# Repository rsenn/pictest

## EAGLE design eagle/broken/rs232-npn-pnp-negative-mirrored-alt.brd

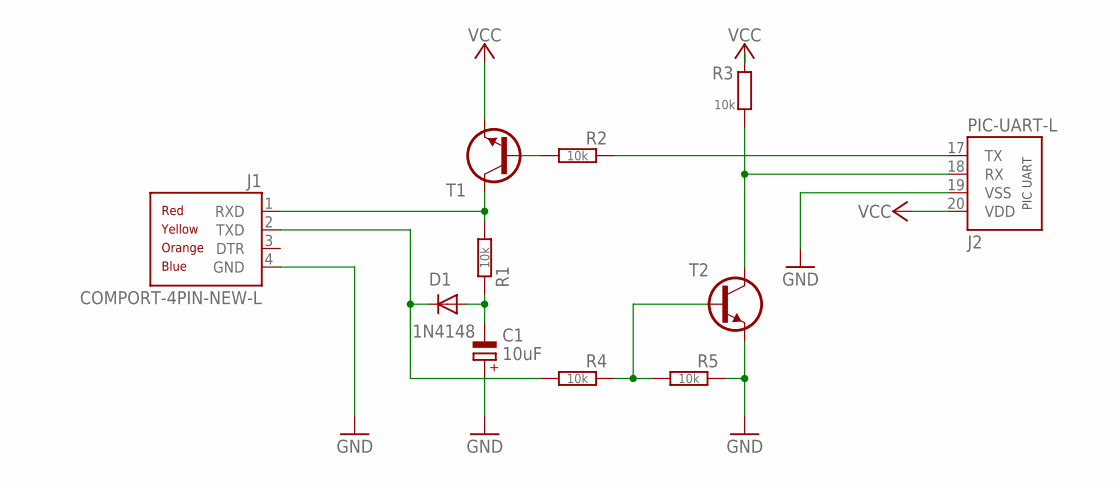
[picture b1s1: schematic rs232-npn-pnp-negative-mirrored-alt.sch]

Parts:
C1: 10uF; E2,5-5
D1: 1N4148; DO34-5V
J1: COMPORT-4PIN-NEW-L; RS232-4PIN-NEW-L
J2: PIC-UART-L
R1, R2, R4: 10k; 0202/7
R3, R5: 10k; 0202/7-V
T1, T2: BC547; TO92-CBE

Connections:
-12V: C1.-, D1.A, R1.1
GND: C1.+, J1.4 (GND), J2.19 (VSS), R5.1, T2.E
unnamed: R2.2, T1.B
unnamed: R4.1, R5.2, T2.B
RX: J2.18 (RX), R3.1, T2.C
RXD: J1.1 (RXD), R1.2, T1.C
TX: J2.17 (TX), R2.1
TXD: D1.C, J1.2 (TXD), R4.2
VCC: J2.20 (VDD), R3.2, T1.E

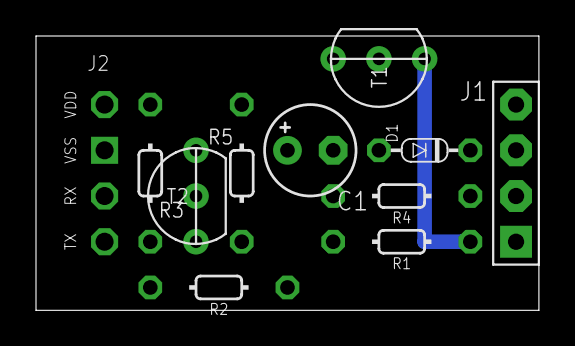
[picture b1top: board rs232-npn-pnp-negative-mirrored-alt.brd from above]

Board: 2 copper layers, 27.9 x 15.2 mm, 11 parts (0 on the bottom side), 9 nets.

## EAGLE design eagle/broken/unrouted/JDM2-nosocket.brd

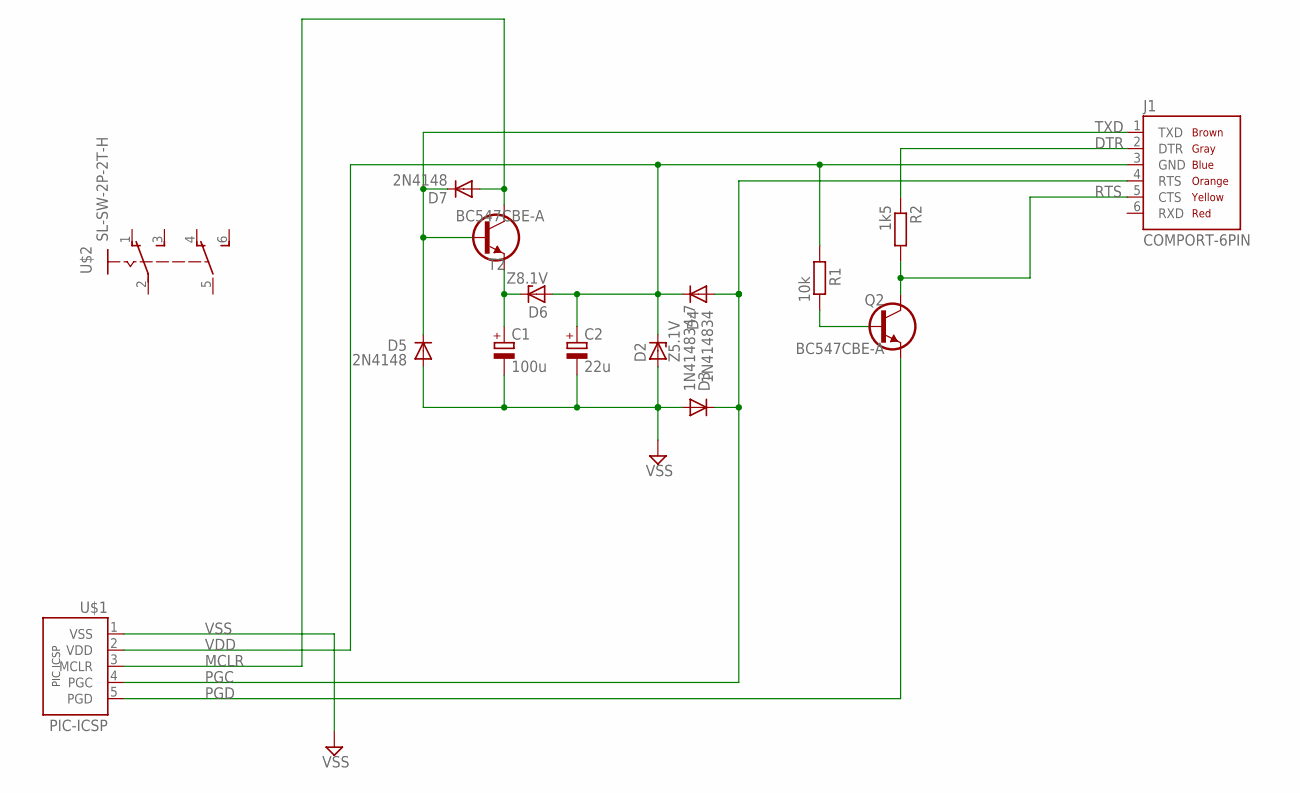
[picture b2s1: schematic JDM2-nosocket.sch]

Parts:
C1: 100u; E2,5-5
C2: 22u; E2,5-4
D2: Z5.1V; DO35Z2_54
D3: 1N414834-7; DO34-7
D4: 1N414834; DO34-7
D5: 2N4148; DO34-7
D6: Z8.1V; DO35Z2_54
D7: 2N4148; DO35-2_54
J1: COMPORT-6PIN; RS232-6PIN
Q2: BC547CBE-A; TO92-CBE-A
R1: 10k; 0204/7
R2: 1k5; 0207/7
T2: BC547CBE-A; TO92-CBE-A
U$1: PIC-ICSP; CONN-5P
U$2: SL-SW-2P-2T-H; SLSW-2P2T-H

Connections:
DTR: J1.2 (DTR), R2.1
MCLR: D7.A, T2.C, U$1.3 (MCLR)
unnamed: Q2.B, R1.1
unnamed: C1.+, D6.C, T2.E
PGC: D3.C, D4.A, J1.4 (RTS), U$1.4 (PGC)
PGD: Q2.E, U$1.5 (PGD)
RTS: J1.5 (CTS), Q2.C, R2.2
TXD: D5.C, D7.C, J1.1 (TXD), T2.B
VDD: C2.+, D2.C, D4.C, D6.A, R1.2, U$1.2 (VDD)
VSS: C1.-, C2.-, D2.A, D3.A, D5.A, U$1.1 (VSS)

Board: 2 copper layers, 15 parts (0 on the bottom side), 10 nets, no tracks yet.

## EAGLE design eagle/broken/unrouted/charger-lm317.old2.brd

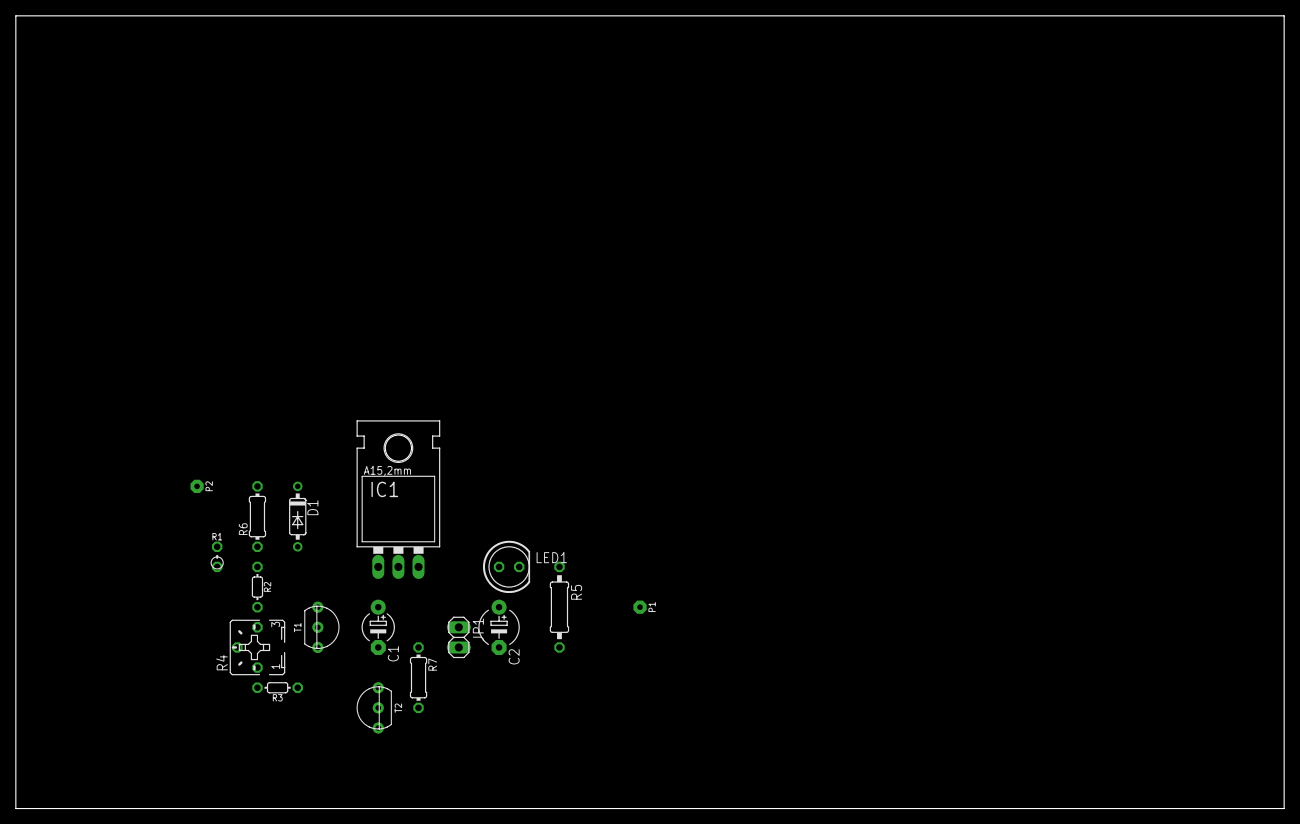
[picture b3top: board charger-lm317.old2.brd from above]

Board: 2 copper layers, 160.0 x 100.0 mm, 17 parts (0 on the bottom side), 11 nets, no tracks yet.

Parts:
C1: E5-4
C2: E5-5
D1: 1N4148-7; DO35-7
IC1: 317TL
JP1: 1X02
LED1: LED5MM
P1, P2: SPAD
R1: 0202/2V
R2, R3: 2.2k; 0202/5
R4: B25P
R5: 0207/10
R6, R7: 0204/7
T1, T2: BC547CBE; TO92-CBE

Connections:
unnamed: C1.+, IC1.1, R4.S, T1.C
unnamed: IC1.2, JP1.1, R3.1
unnamed: C1.-, C2.-, D1.A, R1.2, R6.1, T1.E
unnamed: R2.2, R4.E
unnamed: JP1.2, R1.1, R2.1, R7.1, T1.B
unnamed: D1.C, P2.1, R6.2, T2.E
unnamed: R5.2, T2.C
unnamed: LED1.K, R5.1
unnamed: C2.+, IC1.3, LED1.A, P1.1
unnamed: R3.2, R4.A
unnamed: R7.2, T2.B

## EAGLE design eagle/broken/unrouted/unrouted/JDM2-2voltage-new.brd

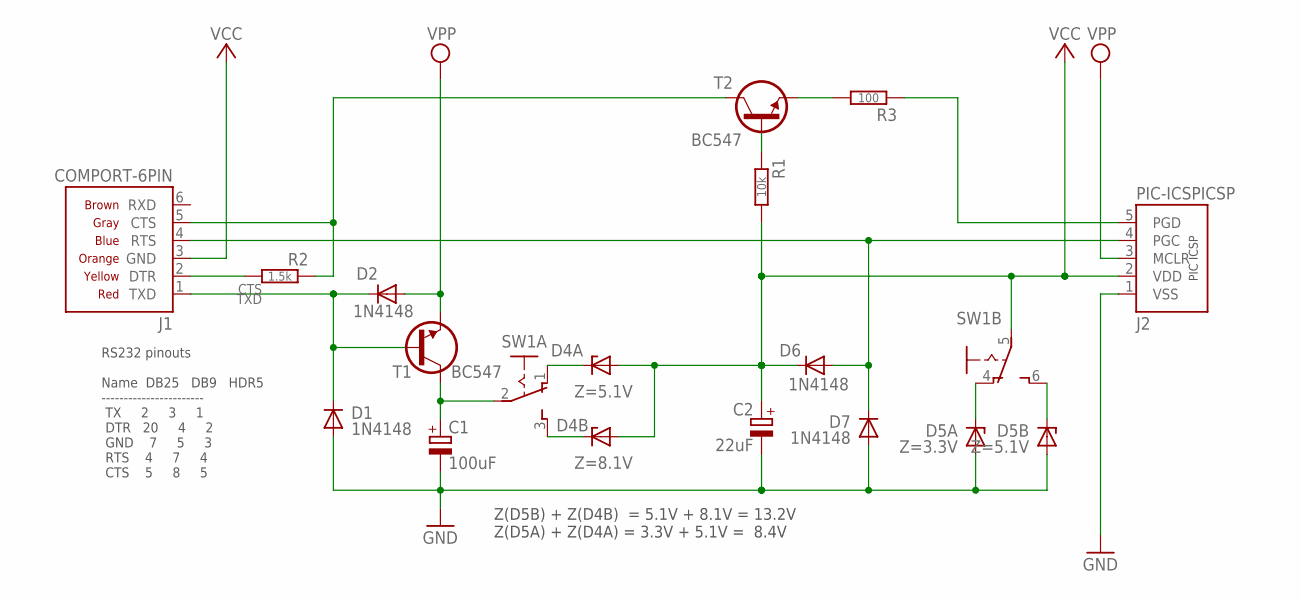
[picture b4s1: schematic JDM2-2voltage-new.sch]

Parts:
C1: 100uF; E2,5-5
C2: 22uF; E2,5-4
D1, D7: 1N4148; DO34-5V
D2, D6: 1N4148; DO34-7V
D4A: Z=5.1V; DO34Z5
D4B: Z=8.1V; DO34Z5
D5A: Z=3.3V; DO34Z7V
D5B: Z=5.1V; DO34Z7V
J1: COMPORT-6PIN; RS232-6PIN
J2: PIC-ICSPICSP; PIC-ICSP
R1: 10k; 0202/7-V
R2: 1.5k; 0202/7-V
R3: 100; 0202/7
SW1: SL-SW-2P-2T-S; SLSW-2P2T-H
T1, T2: BC547; TO92-CBE

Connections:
/MCLR: D2.A, J2.3 (MCLR), T1.E
CLK: D6.A, D7.C, J1.4 (RTS), J2.4 (PGC)
CTS: J1.5 (CTS), R2.1, T2.C
DATA: R3.2, T2.E
GND: C1.-, C2.-, D1.A, D5A.A, D5B.A, D7.A, J2.1 (VSS)
unnamed: R1.1, T2.B
unnamed: D5A.C, SW1.4 (O)
unnamed: D4B.C, SW1.3 (S)
unnamed: C1.+, SW1.2, T1.C
unnamed: D5B.C, SW1.6 (S)
unnamed: J1.2 (DTR), R2.2
PGD: J2.5 (PGD), R3.1
TXD: D1.C, D2.C, J1.1 (TXD), T1.B
VCC: C2.+, D4A.A, D4B.A, D6.C, J1.3 (GND), J2.2 (VDD), R1.2, SW1.5
VPP: D4A.C, SW1.1 (O)

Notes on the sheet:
RS232 pinouts Name DB25 DB9 HDR5 ----------------------- TX 2 3 1 DTR 20 4 2 GND 7 5 3 RTS 4 7 4 CTS 5 8 5
Z(D5B) + Z(D4B) = 5.1V + 8.1V = 13.2V Z(D5A) + Z(D4A) = 3.3V + 5.1V = 8.4V

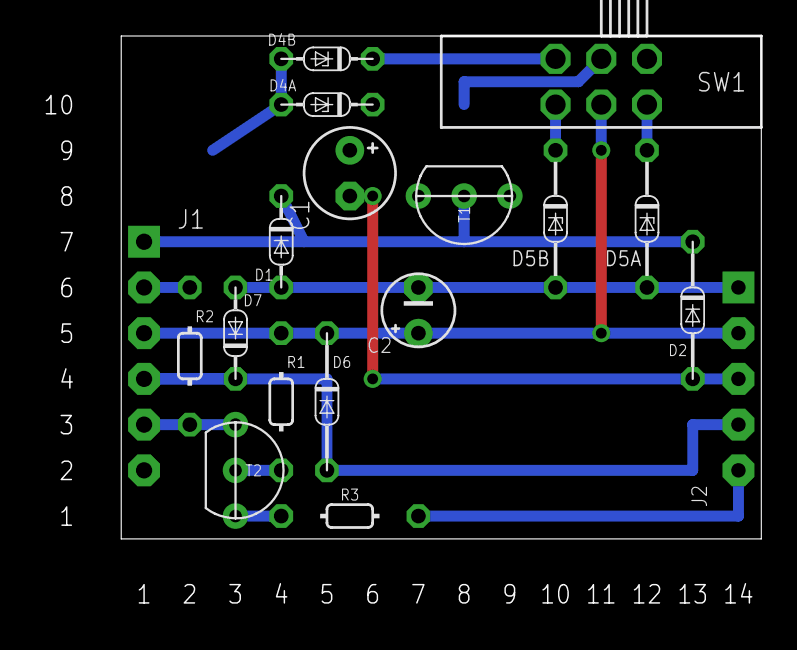
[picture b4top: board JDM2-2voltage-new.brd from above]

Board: 2 copper layers, 35.6 x 27.9 mm, 18 parts (0 on the bottom side), 15 nets.

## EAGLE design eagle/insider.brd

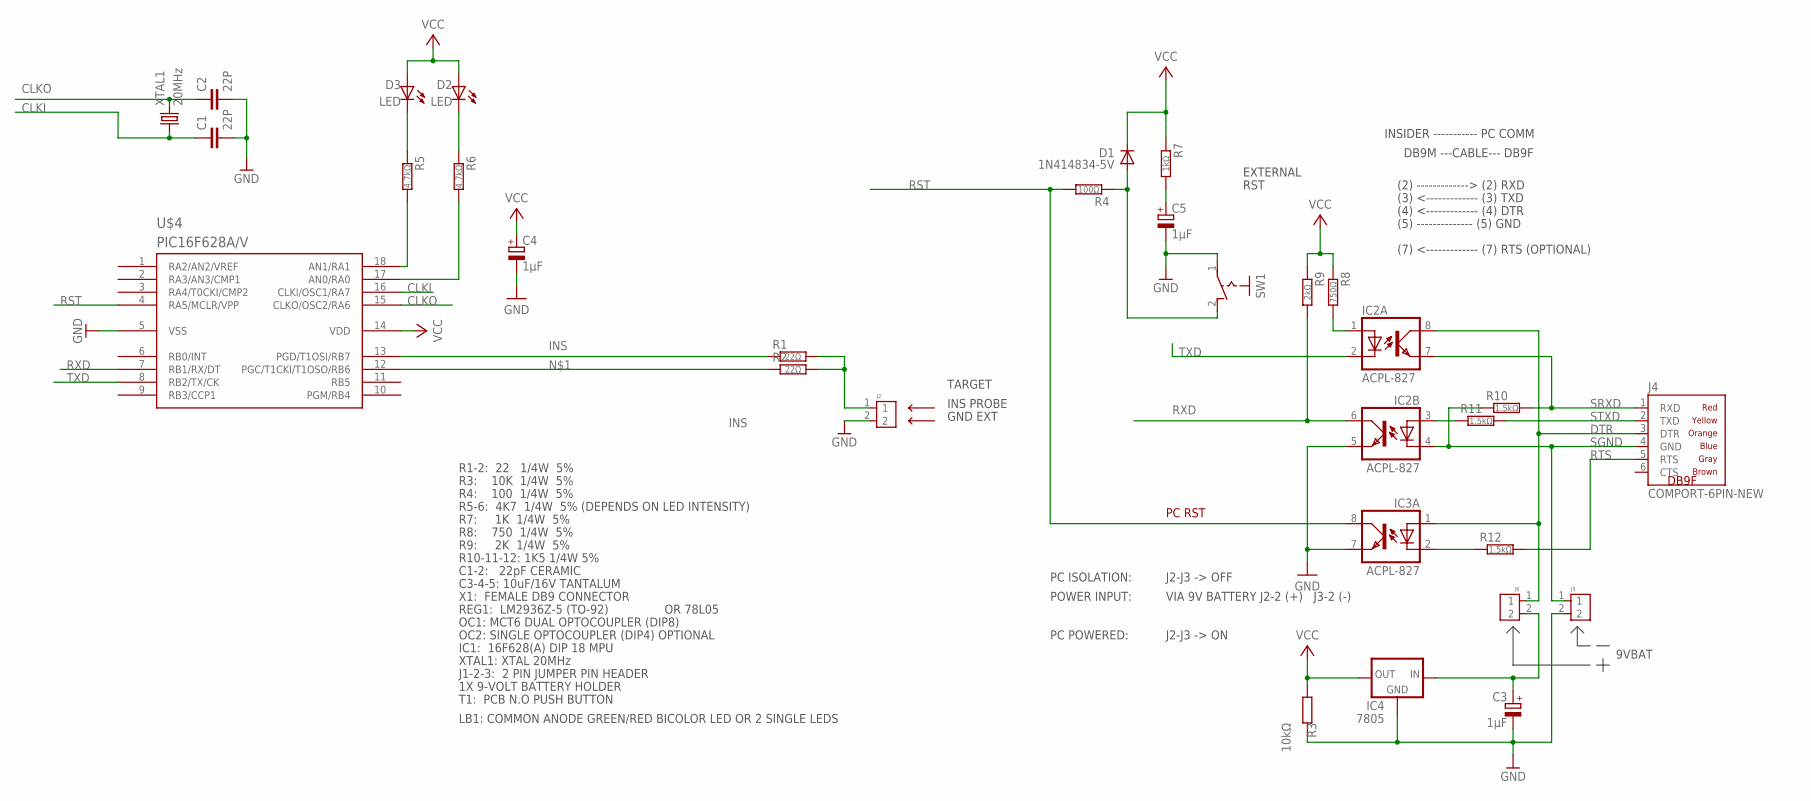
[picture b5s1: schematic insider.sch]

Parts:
C1, C2: 22P; C025-020X036
C3, C4, C5: 1μF; E2.5-4/V
D1: 1N414834-5V; DO34-5V
D2, D3: LED; LED3MM
IC2, IC3: ACPL-827; DIL08
IC4: 7805; TO220
J2, J5, J6: CONN-2P2P/V; CONN-2P-V
J4: COMPORT-6PIN-NEW; RS232-6PIN-NEW
R1, R2: 22Ω; 0204/10
R3: 10kΩ; 0204/10
R4: 100Ω; 0204/15
R5, R6: 4.7kΩ; 0204/10
R7: 1kΩ; 0204/10
R8: 750Ω; 0204/12
R9: 2kΩ; 0204/12
R10, R11, R12: 1.5kΩ; 0204/10
SW1: PB-1P-1T; PB-1P1T
U$4: PIC16F628A/V; DIL18-3/V
XTAL1: 20MHz; HC49

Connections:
CLKI: C1.1, U$4.16 (CLKI/OSC1/RA7), XTAL1.1
CLKO: C2.1, U$4.15 (CLKO/OSC2/RA6), XTAL1.2
DTR: IC2.8 (COL), IC3.1 (A), J4.3 (DTR), J6.1
GND: C1.2, C2.2, C3.-, C4.-, C5.-, IC2.5 (EMIT), IC3.7 (EMIT), IC4.2 (GND), J2.2, J5.2, R3.2, SW1.1, U$4.5 (VSS)
INS: R1.1, U$4.13 (PGD/T1OSI/RB7)
unnamed: R2.1, U$4.12 (PGC/T1CKI/T1OSO/RB6)
unnamed: R5.2, U$4.18 (AN1/RA1)
unnamed: IC2.3 (A), R11.1
unnamed: IC2.1 (A), R8.2
unnamed: IC3.2 (C), R12.1
unnamed: J2.1, R1.2, R2.2
unnamed: R6.2, U$4.17 (AN0/RA0)
unnamed: C5.+, R7.2
unnamed: D2.K (C), R6.1
unnamed: D3.K (C), R5.1
unnamed: D1.A, R4.1, SW1.2 (S)
unnamed: C3.+, IC4.1 (IN), J6.2
RST: IC3.8 (COL), R4.2, U$4.4 (RA5/MCLR/VPP)
RTS: J4.5 (RTS), R12.2
RXD: IC2.6 (COL), R9.2, U$4.7 (RB1/RX/DT)
SGND: IC2.4 (C), J4.4 (GND), J5.1, R10.1
SRXD: IC2.7 (EMIT), J4.1 (RXD), R10.2
STXD: J4.2 (TXD), R11.2
TXD: IC2.2 (C), U$4.8 (RB2/TX/CK)
VCC: C4.+, D1.C, D2.A, D3.A, IC4.3 (OUT), R3.1, R7.1, R8.1, R9.1, U$4.14 (VDD)

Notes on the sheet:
EXTERNAL
RST
9VBAT
GND EXT
INS PROBE
PC ISOLATION:
J2-J3 -> OFF
POWER INPUT:
VIA 9V BATTERY J2-2 (+) J3-2 (-)
PC POWERED:
J2-J3 -> ON
TARGET
PC RST
R1-2: 22 1/4W 5%
R3: 10K 1/4W 5%
R4: 100 1/4W 5%
R5-6: 4K7 1/4W 5% (DEPENDS ON LED INTENSITY)
R7: 1K 1/4W 5%
R8: 750 1/4W 5%
R10-11-12: 1K5 1/4W 5%
R9: 2K 1/4W 5%
C1-2: 22pF CERAMIC
C3-4-5: 10uF/16V TANTALUM
REG1: LM2936Z-5 (TO-92)
OR 78L05
OC1: MCT6 DUAL OPTOCOUPLER (DIP8)
OC2: SINGLE OPTOCOUPLER (DIP4) OPTIONAL
IC1: 16F628(A) DIP 18 MPU
XTAL1: XTAL 20MHz
J1-2-3: 2 PIN JUMPER PIN HEADER
1X 9-VOLT BATTERY HOLDER
LB1: COMMON ANODE GREEN/RED BICOLOR LED OR 2 SINGLE LEDS
X1: FEMALE DB9 CONNECTOR
(2) -------------> (2) RXD
(3) <------------- (3) TXD
(4) <------------- (4) DTR
(5) -------------- (5) GND
INSIDER ----------- PC COMM
DB9M ---CABLE--- DB9F
DB9F

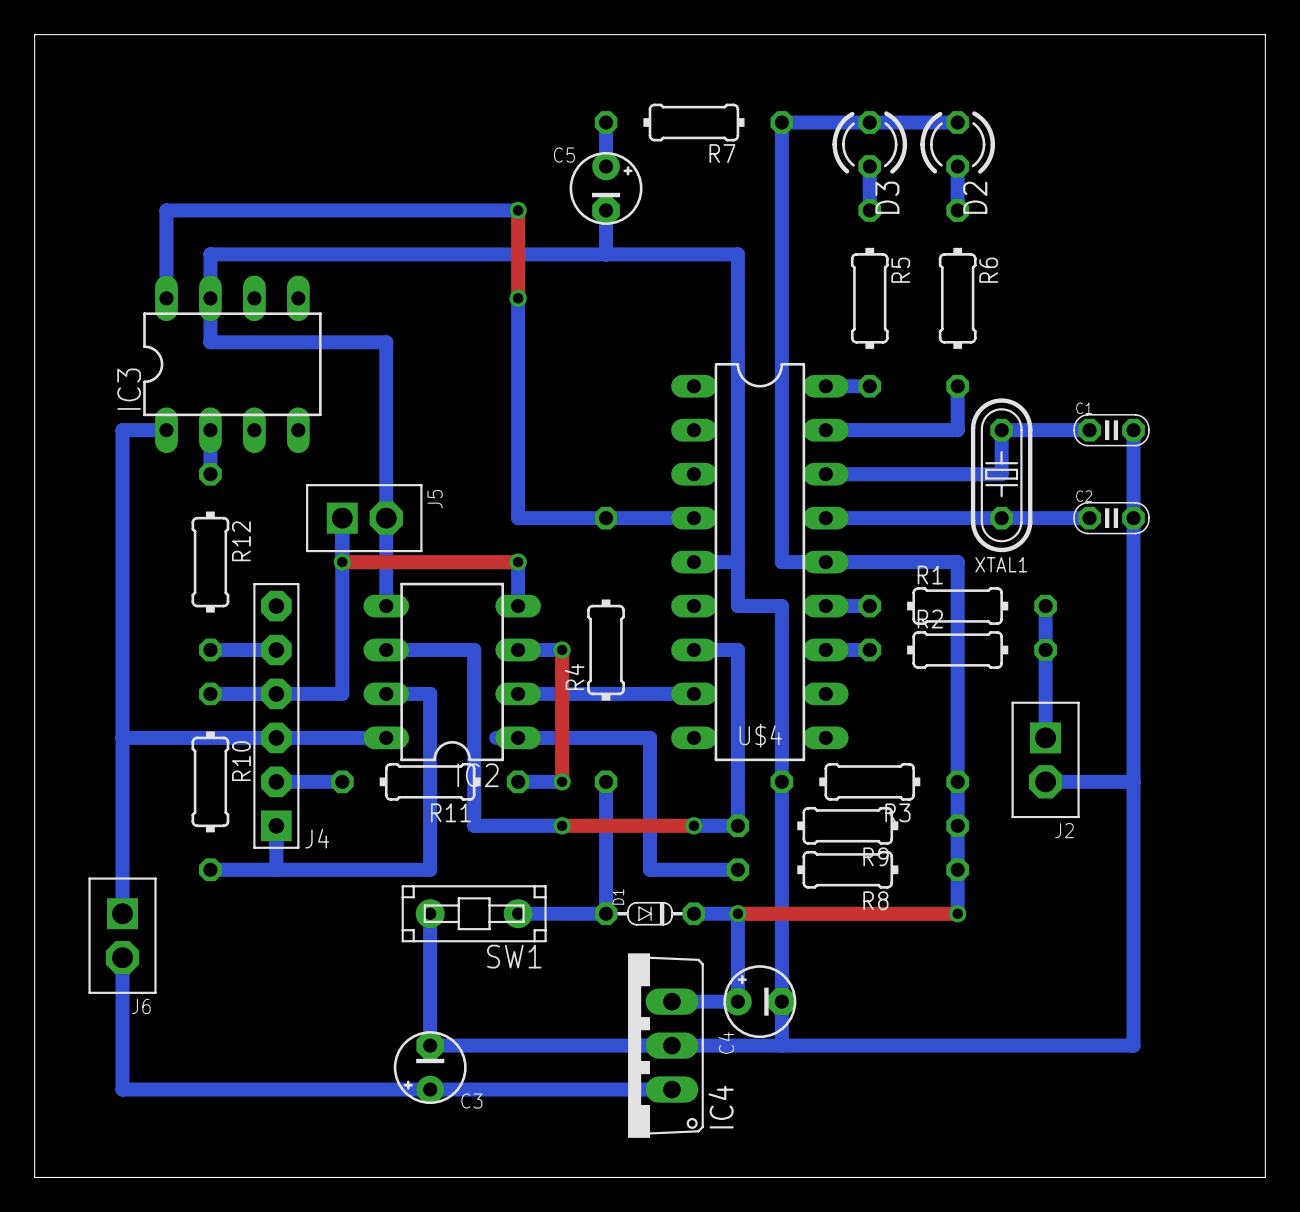
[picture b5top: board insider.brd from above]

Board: 2 copper layers, 71.1 x 66.0 mm, 30 parts (0 on the bottom side), 25 nets.

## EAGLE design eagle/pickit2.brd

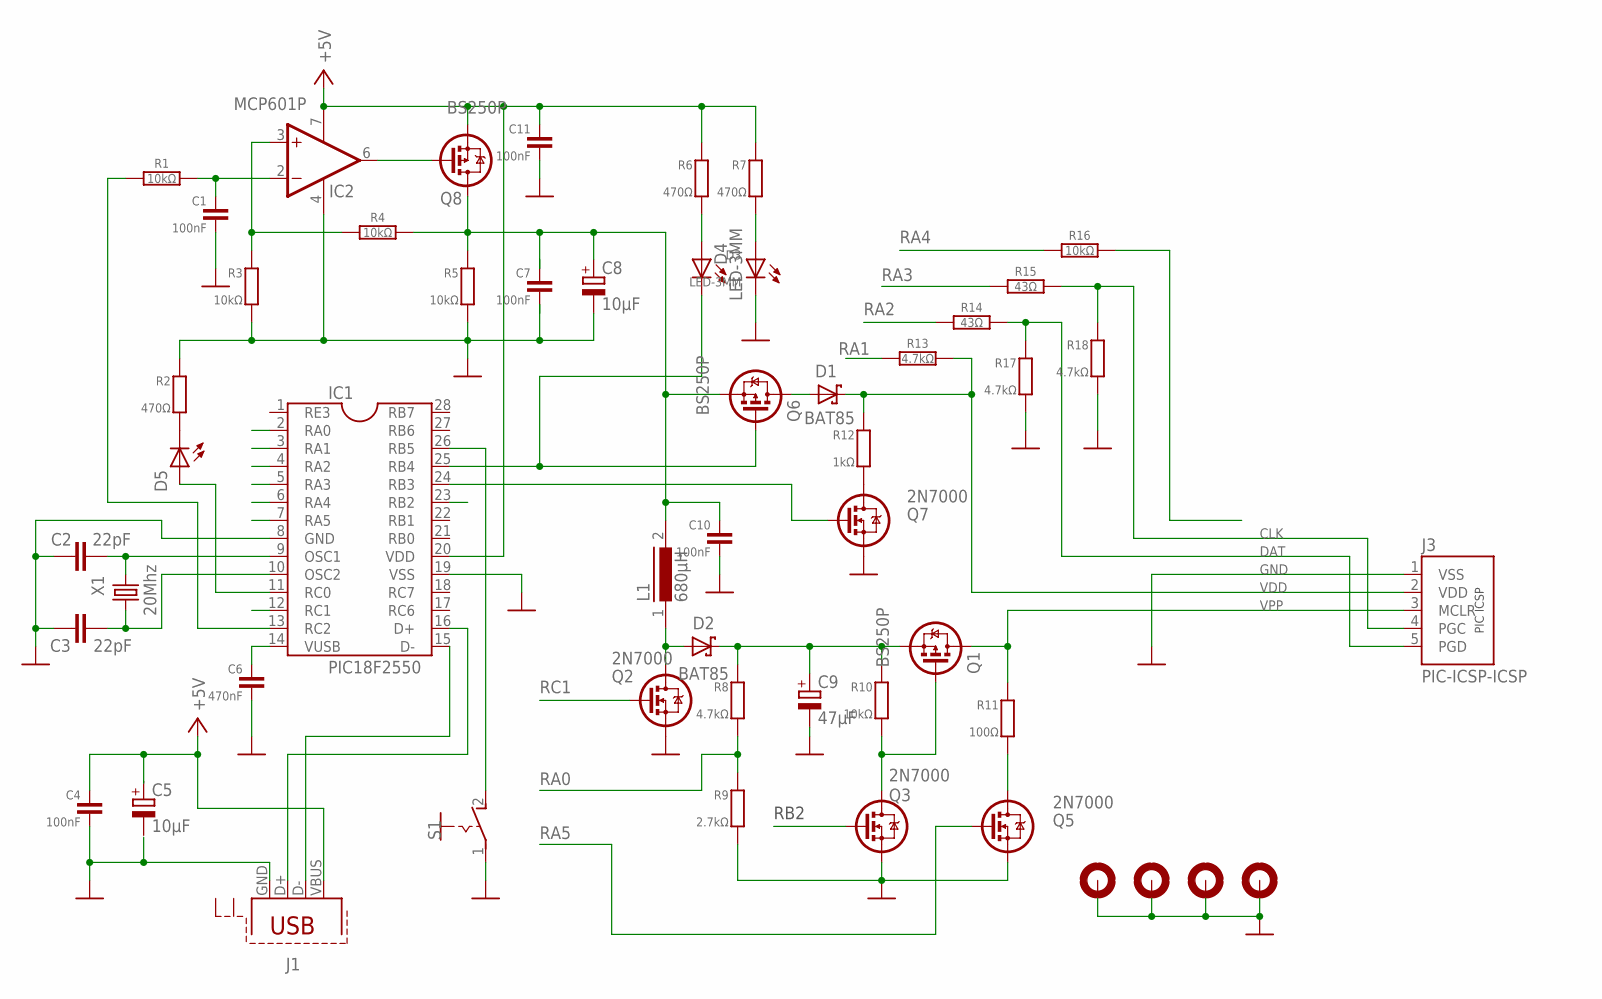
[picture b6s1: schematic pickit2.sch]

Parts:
C1, C4, C7, C10, C11: 100nF; C050-025X075/V
C2, C3: 22pF; C2.5-2
C5, C8: 10μF; E2,5-5
C6: 470nF; C050-025X075/V
C9: 47μF; E2,5-5
D1, D2: BAT85; DO35-10M
D3, D4: LED-3MM; LED_3MM
D5: LED5MM
H1, H2, H3, H4: MOUNT-PAD-ROUND2.8; 2,8-PAD
IC1: PIC18F2550; DIL28
IC2: MCP601P; DIL08M
J1: PN61729-S
J3: PIC-ICSP-ICSP; PIC-ICSP
L1: 680μH; R0608
Q1, Q6, Q8: BS250P; TO92
Q2, Q3, Q5, Q7: 2N7000; TO92
R1, R3, R4, R5, R10, R16: 10kΩ; 0204/10
R2, R6, R7: 470Ω; 0204/10
R8, R13, R17, R18: 4.7kΩ; 0204/10
R9: 2.7kΩ; 0204/10
R11: 100Ω; 0204/10
R12: 1kΩ; 0204/10
R14, R15: 43Ω; 0204/10
S1: PB-1P-1T; PB-1P1T
X1: 20Mhz; HC49

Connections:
+5V: C4.1, C5.+, C11.1, IC1.20 (VDD), IC2.7 (V+), J1.VBUS (1), Q8.3 (S), R6.1, R7.1
GND: C1.2, C2.1, C3.2, C4.2, C6.2, C7.2, C8.-, C9.-, C10.2, C11.2, D3.K (C), H1.B2,8, H2.B2,8, H3.B2,8, H4.B2,8, IC1.8 (GND), IC1.19 (VSS), IC2.4 (V-), J1.GND (4), J3.1 (VSS), Q2.1 (S), Q3.1 (S), Q5.1 (S), Q7.1 (S), R2.1, R3.2, R5.2, R9.2, R17.2, R18.2, S1.1
unnamed: D4.A, R6.2
unnamed: D2.A, L1.1, Q2.3 (D)
unnamed: IC2.6 (OUT), Q8.2 (G)
unnamed: C9.+, D2.C, Q1.3 (S), R8.1, R10.1
unnamed: D3.A, R7.2
unnamed: D5.K (C), R2.2
unnamed: Q5.3 (D), R11.2
unnamed: IC1.15 (D-), J1.D- (2)
unnamed: IC1.16 (D+), J1.D+ (3)
unnamed: Q1.2 (G), Q3.3 (D), R10.2
unnamed: J3.3 (MCLR), Q1.1 (D), R11.1
unnamed: D1.A, Q6.1 (D)
unnamed: D1.C, J3.2 (VDD), R12.1, R13.2
unnamed: Q7.3 (D), R12.2
unnamed: D4.K (C), IC1.25 (RB4), Q6.2 (G)
unnamed: C2.2, IC1.9 (OSC1), X1.2
unnamed: C6.1, IC1.14 (VUSB)
unnamed: IC1.24 (RB3), Q7.2 (G)
unnamed: J3.5 (PGD), R14.2, R17.1
unnamed: J3.4 (PGC), R15.2, R18.1
unnamed: IC2.3 (+IN), R3.1, R4.1
unnamed: C7.1, C8.+, C10.1, L1.2, Q6.3 (S), Q8.1 (D), R4.2, R5.1
unnamed: C3.1, IC1.10 (OSC2), X1.1
unnamed: C1.1, IC2.2 (-IN), R1.2
RA0: IC1.2 (RA0), R8.2, R9.1
RA1: IC1.3 (RA1), R13.1
RA2: IC1.4 (RA2), R14.1
RA3: IC1.5 (RA3), R15.1
RA4: IC1.6 (RA4), R16.1
RA5: IC1.7 (RA5), Q5.2 (G)
RB2: IC1.23 (RB2), Q3.2 (G)
RB5: IC1.26 (RB5), S1.2 (S)
RC0: D5.A, IC1.11 (RC0)
RC1: IC1.12 (RC1), Q2.2 (G)
RC2: IC1.13 (RC2), R1.1

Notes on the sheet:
RB2
VPP
VDD
GND
DAT
CLK

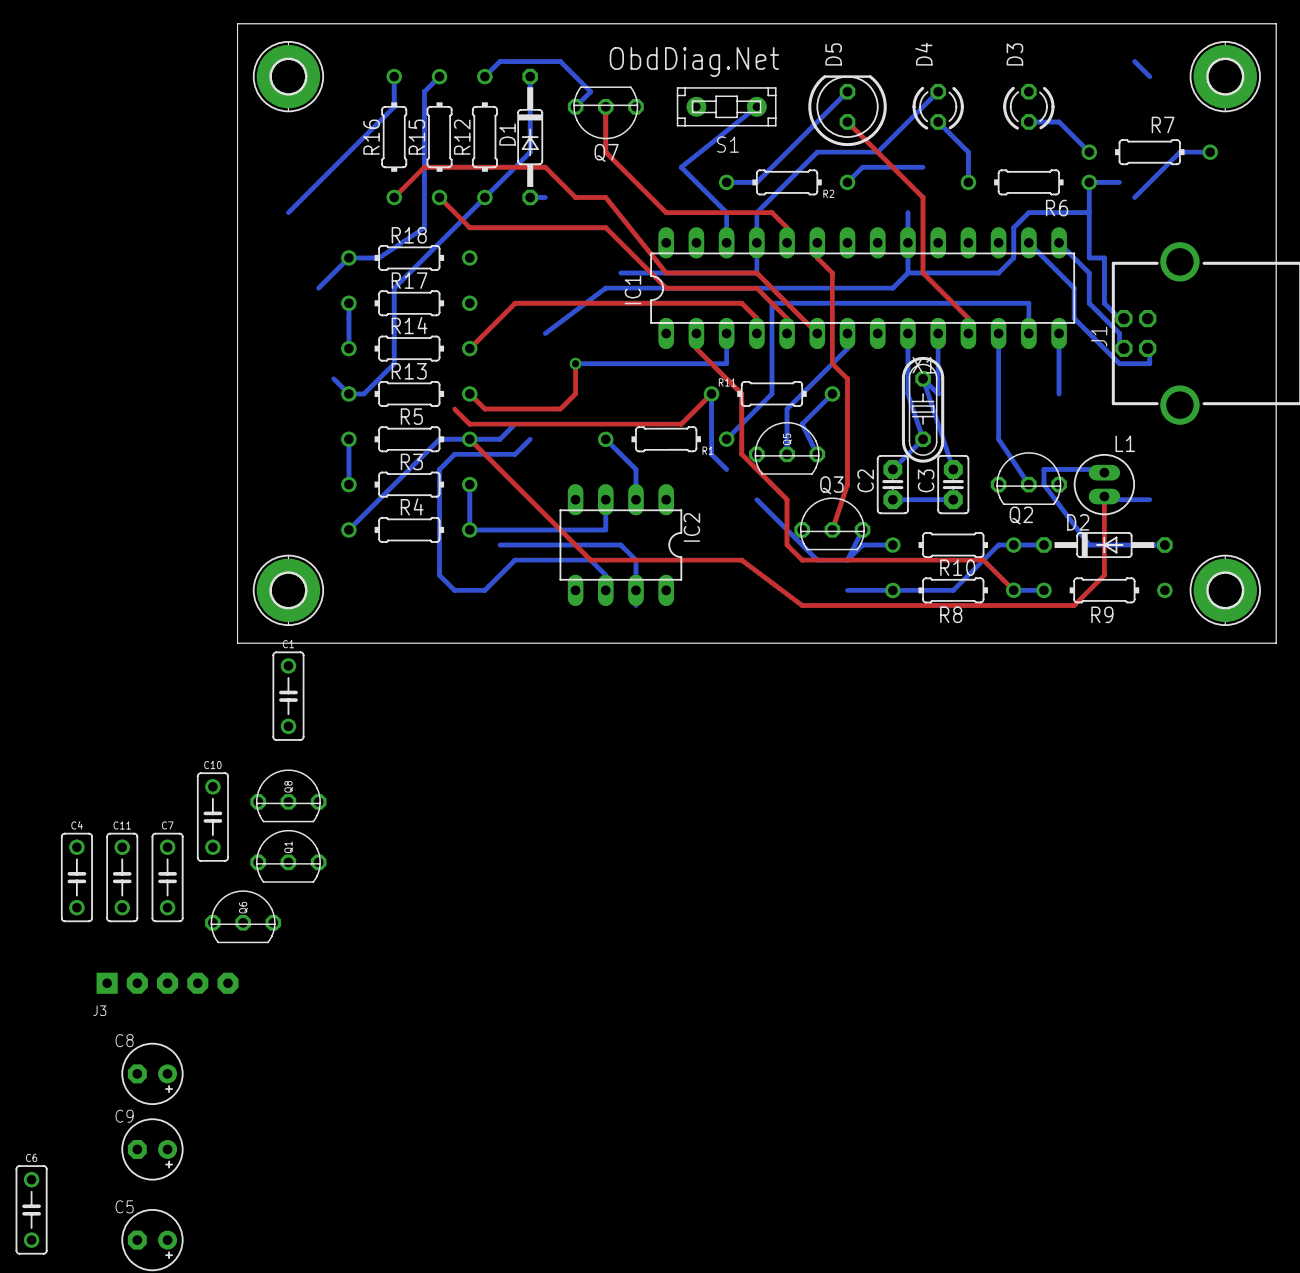
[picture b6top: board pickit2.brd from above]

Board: 2 copper layers, 87.3 x 52.1 mm, 52 parts (0 on the bottom side), 37 nets.
